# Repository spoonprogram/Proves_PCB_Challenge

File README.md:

# Proves_PCB_Challenge
PCB Challenge Submission

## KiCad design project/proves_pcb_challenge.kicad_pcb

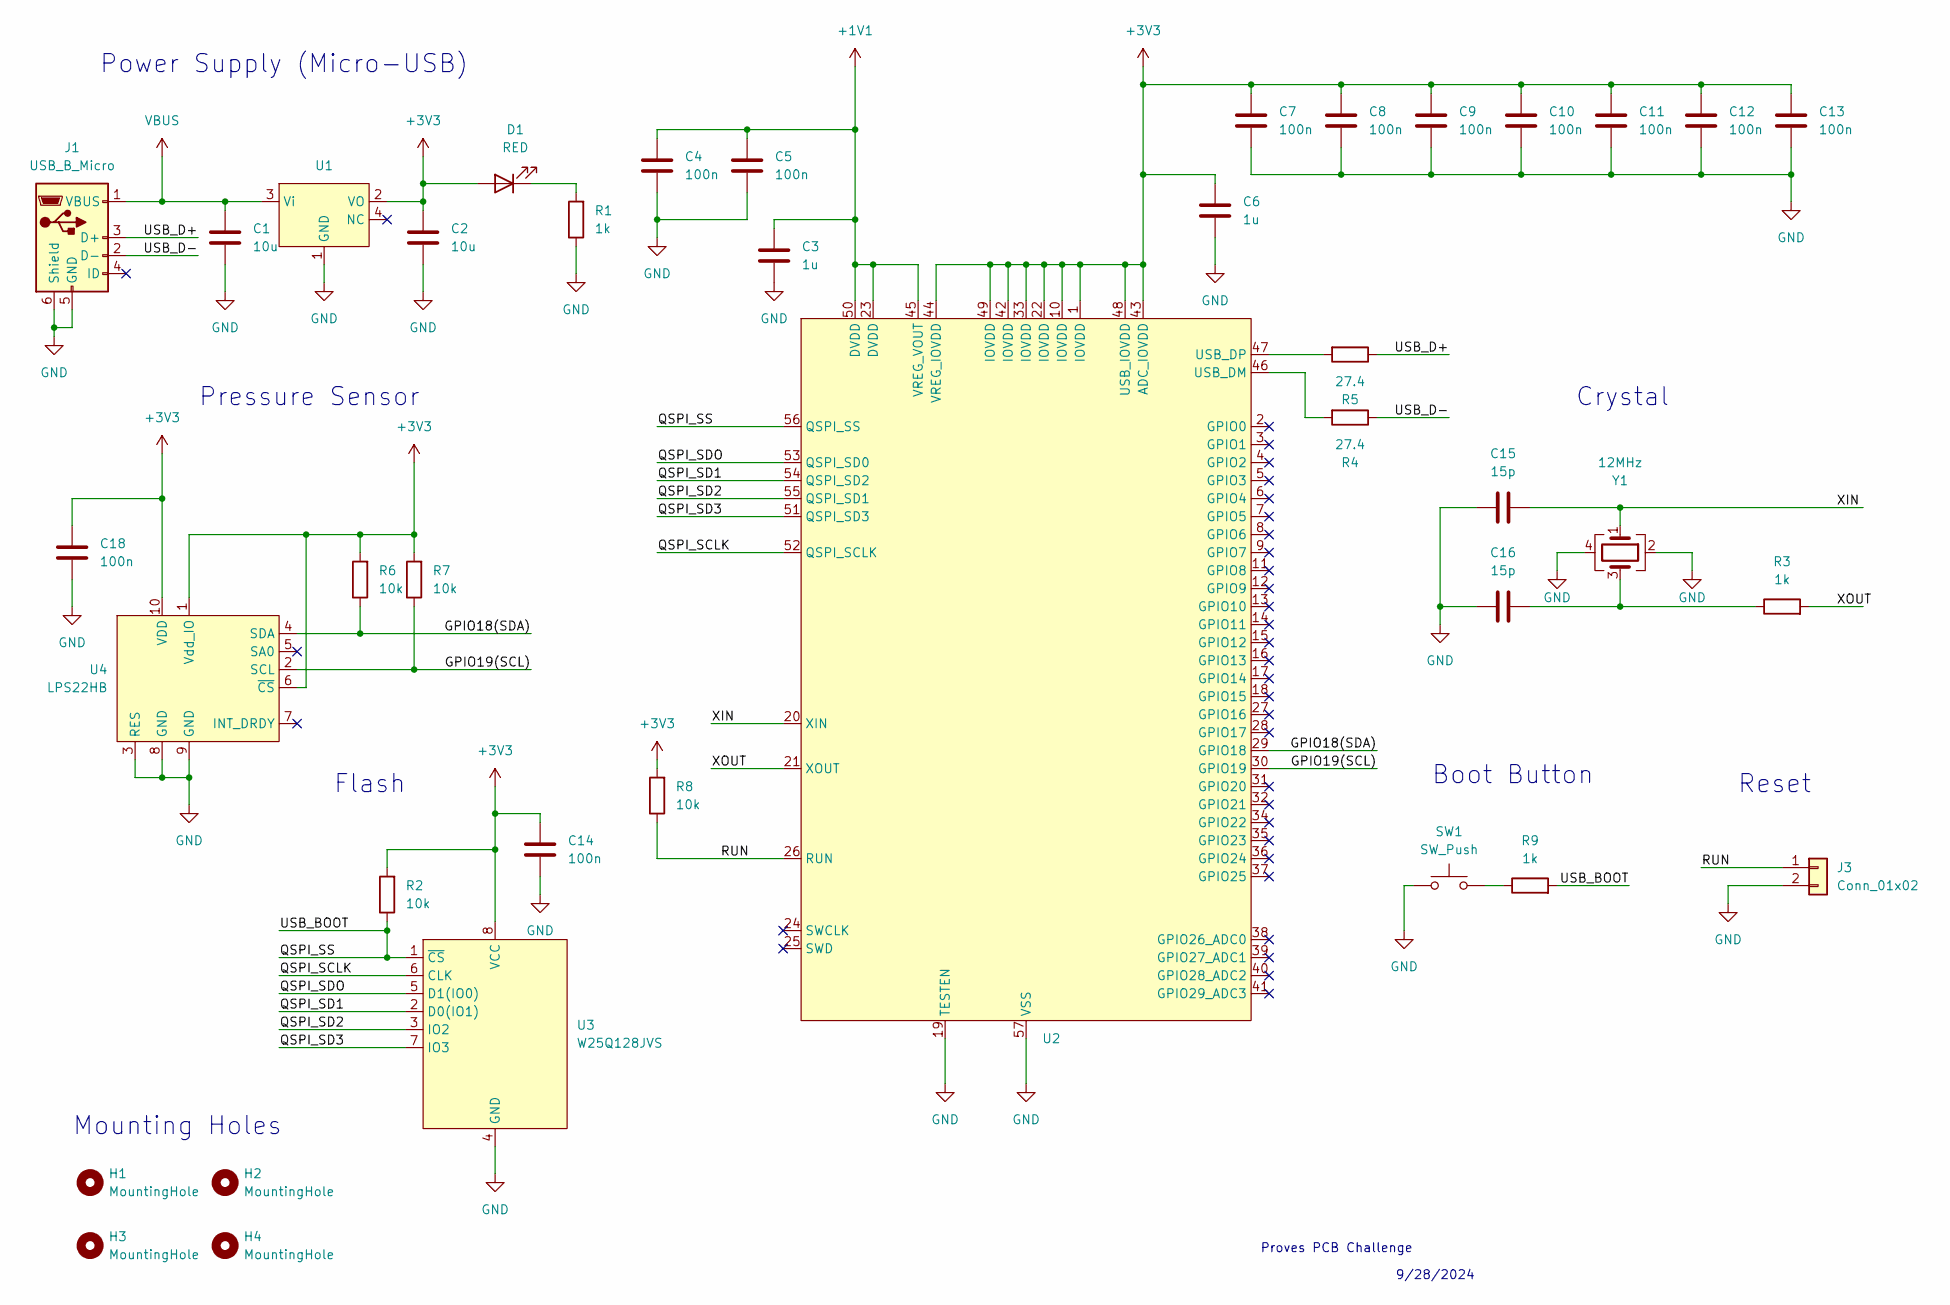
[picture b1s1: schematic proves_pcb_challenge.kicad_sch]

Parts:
C1, C2: 10u; C_0603_1608Metric
C3, C6: 1u; C_0402_1005Metric
C4, C5, C7, C8, C9, C10, C11, C12, C13, C14, C18: 100n; C_0402_1005Metric
C15, C16: 15p; C_0402_1005Metric
D1: RED; LED_0603_1608Metric
H1, H2, H3, H4: MountingHole; MountingHole_2.2mm_M2
J1: USB_B_Micro; USB_Micro-B_Amphenol_10104110_Horizontal
J3: Conn_01x02; PinHeader_1x02_P2.54mm_Vertical
R1, R3, R9: 1k; R_0402_1005Metric
R2, R6, R7, R8: 10k; R_0402_1005Metric
R4, R5: 27.4; R_0402_1005Metric
SW1: SW_Push; SW_SPST_PTS810
U1: SOT-223
U2: QFN-56-1EP_7x7mm_P0.4mm_EP3.2x3.2mm
U3: W25Q128JVS; SOIC-8W_5.3x5.3mm_P1.27mm
U4: LPS22HB; ST_HLGA-10_2x2mm_P0.5mm_LayoutBorder3x2y
Y1: 12MHz; Crystal_SMD_Abracon_ABM8AIG-4Pin_3.2x2.5mm

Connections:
+1V1: C3.1, C4.1, C5.1, U2.23 (DVDD), U2.45 (VREG_VOUT), U2.50 (DVDD)
+3V3: C2.1, C6.1, C7.1, C8.1, C9.1, C10.1, C11.1, C12.1, C13.1, C14.1, C18.1, D1.2 (A), R2.2, R6.2, R7.2, R8.2, U1.2 (VO), U2.1 (IOVDD), U2.10 (IOVDD), U2.22 (IOVDD), U2.33 (IOVDD), U2.42 (IOVDD), U2.43 (ADC_IOVDD), U2.44 (VREG_IOVDD), U2.48 (USB_IOVDD), U2.49 (IOVDD), U3.8 (VCC), U4.1 (Vdd_IO), U4.6 (~CS), U4.10 (VDD)
/GPIO18(SDA): R6.1, U2.29 (GPIO18), U4.4 (SDA)
/GPIO19(SCL): R7.1, U2.30 (GPIO19), U4.2 (SCL)
/QSPI_SCLK: U2.52 (QSPI_SCLK), U3.6 (CLK)
/QSPI_SD1: U2.54 (QSPI_SD2), U3.2 (D0(IO1))
/QSPI_SD2: U2.55 (QSPI_SD1), U3.3 (IO2)
/QSPI_SD3: U2.51 (QSPI_SD3), U3.7 (IO3)
/QSPI_SDO: U2.53 (QSPI_SD0), U3.5 (D1(IO0))
/QSPI_SS: R2.1, R9.2, U2.56 (QSPI_SS), U3.1 (~CS)
/RUN: J3.1, R8.1, U2.26 (RUN)
/USB_D+: J1.3 (D+), R5.1
/USB_D-: J1.2 (D-), R4.1
/XIN: C15.2, U2.20 (XIN), Y1.1
/XOUT: R3.2, U2.21 (XOUT)
GND: C1.2, C2.2, C3.2, C4.2, C5.2, C6.2, C7.2, C8.2, C9.2, C10.2, C11.2, C12.2, C13.2, C14.2, C15.1, C16.1, C18.2, J1.5 (GND), J1.6 (Shield), J3.2, R1.1, SW1.1, U1.1 (GND), U2.19 (TESTEN), U2.57 (VSS), U3.4 (GND), U4.3 (RES), U4.8 (GND), U4.9 (GND), Y1.2, Y1.4
unnamed: C16.2, R3.1, Y1.3
unnamed: D1.1 (K), R1.2
unnamed: R9.1, SW1.2
unnamed: R4.2, U2.46 (USB_DM)
unnamed: R5.2, U2.47 (USB_DP)
VBUS: C1.1, J1.1 (VBUS), U1.3 (Vi)

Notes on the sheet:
Flash
Power Supply (Micro-USB)
9/28/2024
Crystal
Boot Button
Reset
Mounting Holes
Proves PCB Challenge
Pressure Sensor

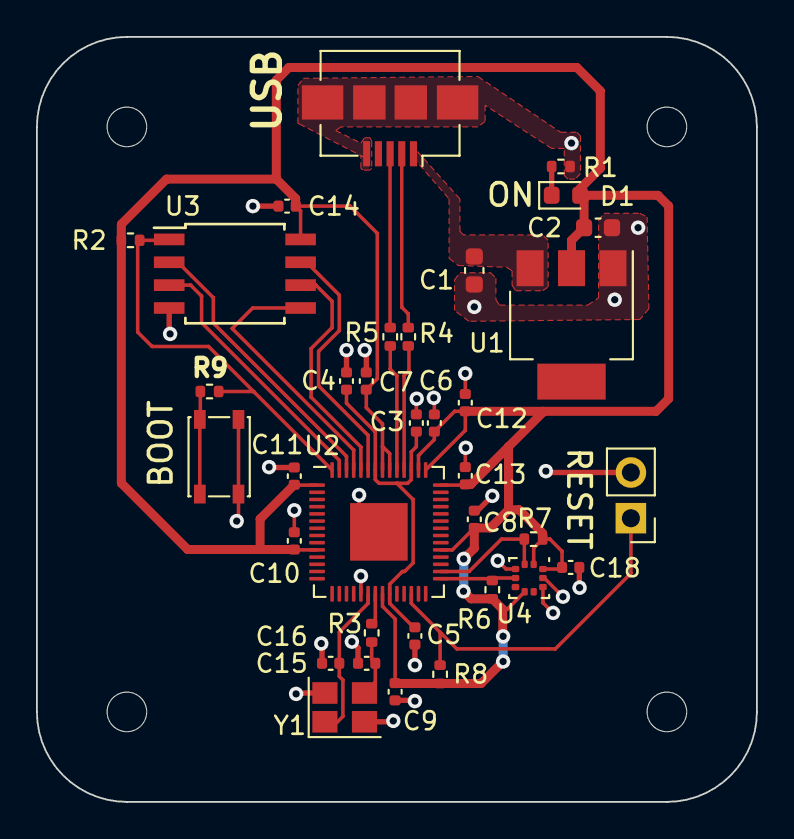
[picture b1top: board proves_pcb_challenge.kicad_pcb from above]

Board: 2 copper layers, 40.0 x 42.5 mm, 39 parts (0 on the bottom side), 22 nets.

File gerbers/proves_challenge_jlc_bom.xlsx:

Comment | Designator | Footprint | JLCPCB Part#
10u | C1, C2 | Capacitor_SMD:C_0603_1608Metric | C329937
1u | C3, C6 | Capacitor_SMD:C_0402_1005Metric | C694169
100n | C4, C5, C7, C8, C9, C10, C11, C12, C13, C14, C18 | Capacitor_SMD:C_0402_1005Metric | C2167110
15p | C15, C16 | Capacitor_SMD:C_0402_1005Metric | C694267
Red LED | D1 | LED_SMD:LED_0603_1608Metric | C128249
USB B Micro | J1 | Connector_USB:USB_Micro-B_Amphenol_10104110_Horizontal | C2931352
Conn_01x02 | J3 | Connector_PinHeader_2.54mm:PinHeader_1x02_P2.54mm_Vertical | C7427687
1k | R1, R3, R9 | Resistor_SMD:R_0402_1005Metric | C102748
10k | R2, R6-R8 | Resistor_SMD:R_0402_1005Metric | C176114
27.4 | R4, R5 | Resistor_SMD:R_0402_1005Metric | C321420
SW_Push | SW1 | Button_Switch_SMD:SW_SPST_PTS810 | C116501
NCP1117 | U1 | Package_TO_SOT_SMD:SOT-223 | C2902119
RP2040 | U2 | Package_DFN_QFN:QFN-56-1EP_7x7mm_P0.4mm_EP3.2x3.2mm | C2040
W25Q128JVS | U3 | Package_SO:SOIC-8W_5.3x5.3mm_P1.27mm | C97521
LPS22HB | U4 | Package_LGA:ST_HLGA-10_2x2mm_P0.5mm_LayoutBorder3x2y | C94049
12MHz | Y1 | Crystal:Crystal_SMD_Abracon_ABM8AIG-4Pin_3.2x2.5mm | C20625731

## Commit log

2024-09-30 Rename proves_challenge_jlc_bom.xlsx to gerbers/proves_challenge_jlc_bom.xlsx
2024-09-30 Rename gerbers/proves_challenge_jlc_bom.xlsx to proves_challenge_jlc_bom.xlsx
